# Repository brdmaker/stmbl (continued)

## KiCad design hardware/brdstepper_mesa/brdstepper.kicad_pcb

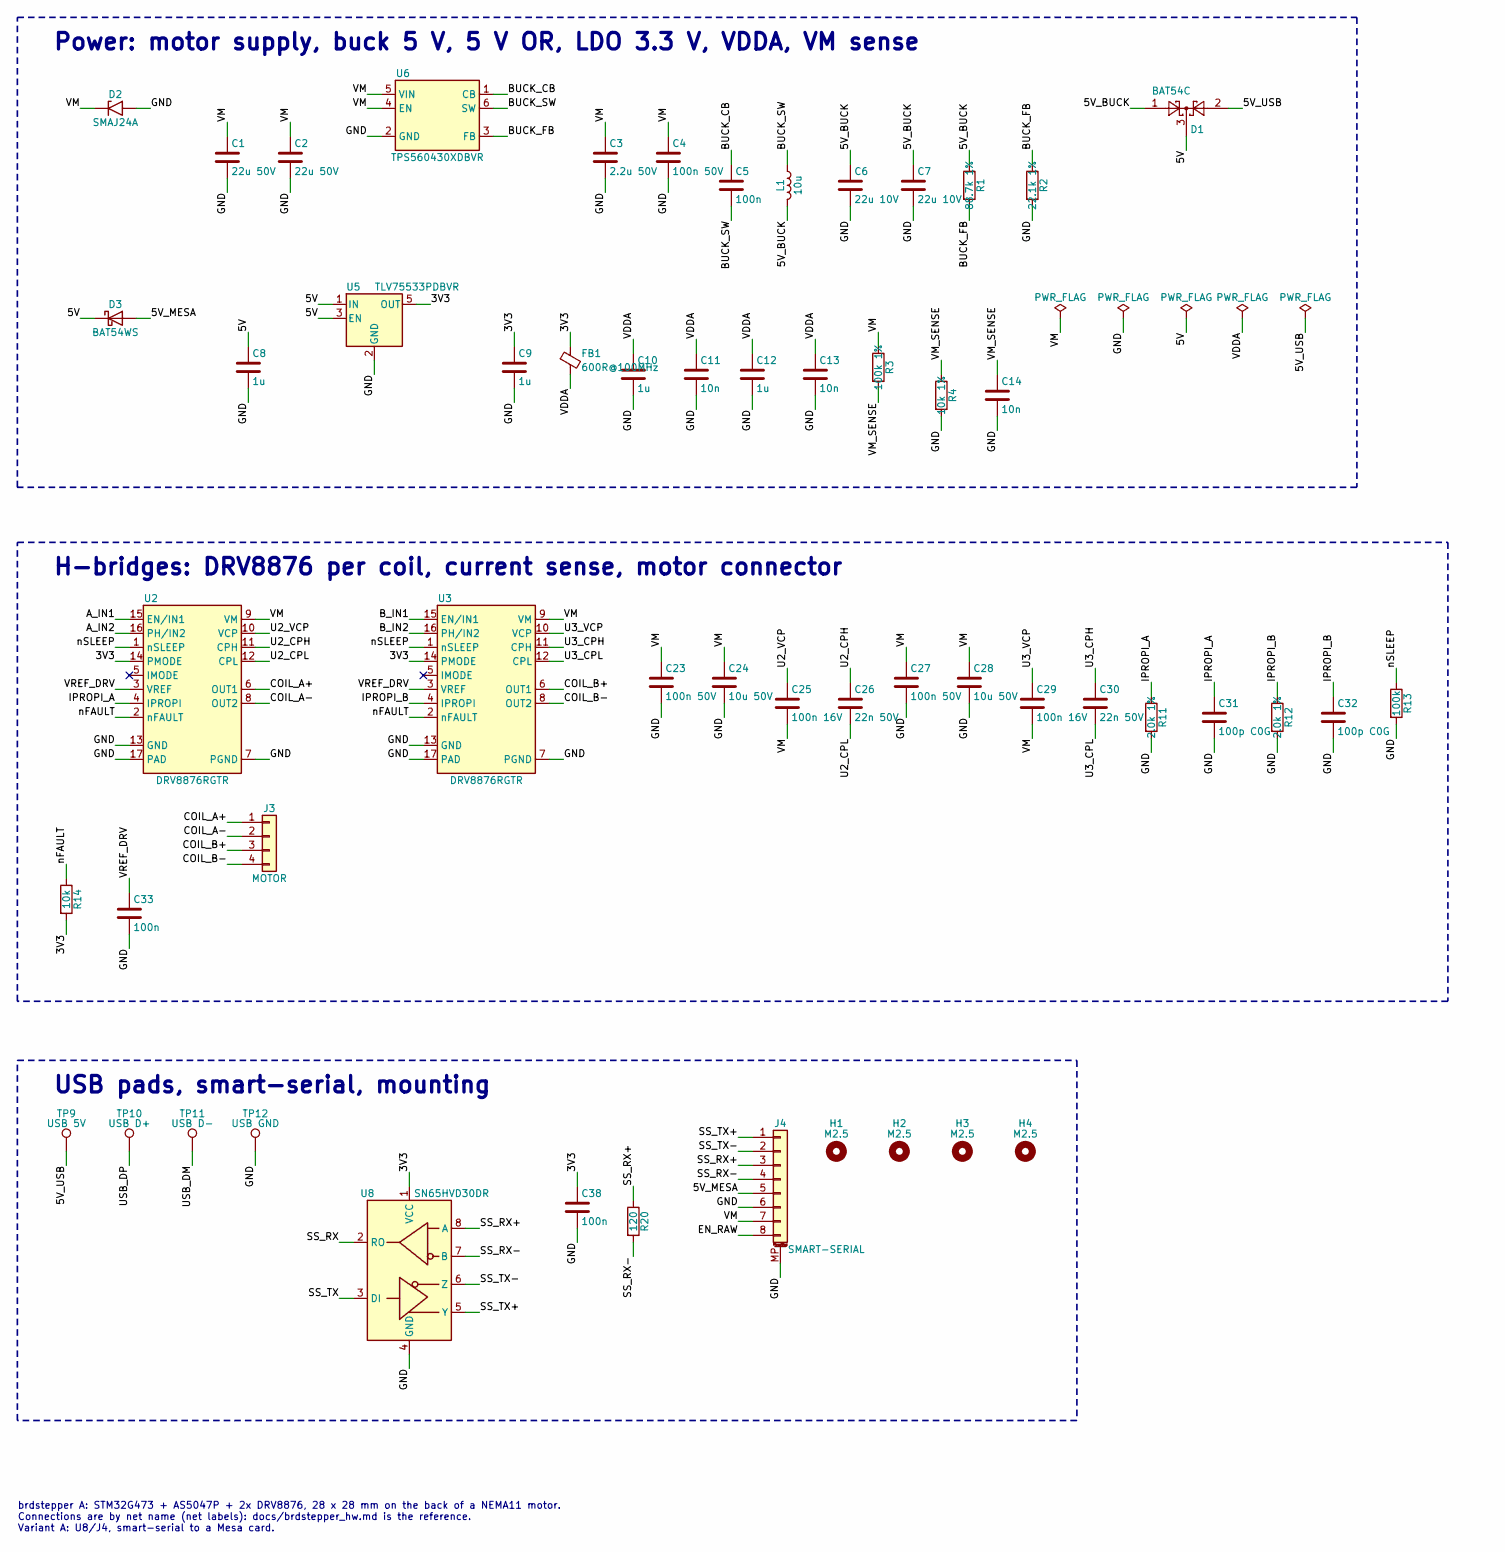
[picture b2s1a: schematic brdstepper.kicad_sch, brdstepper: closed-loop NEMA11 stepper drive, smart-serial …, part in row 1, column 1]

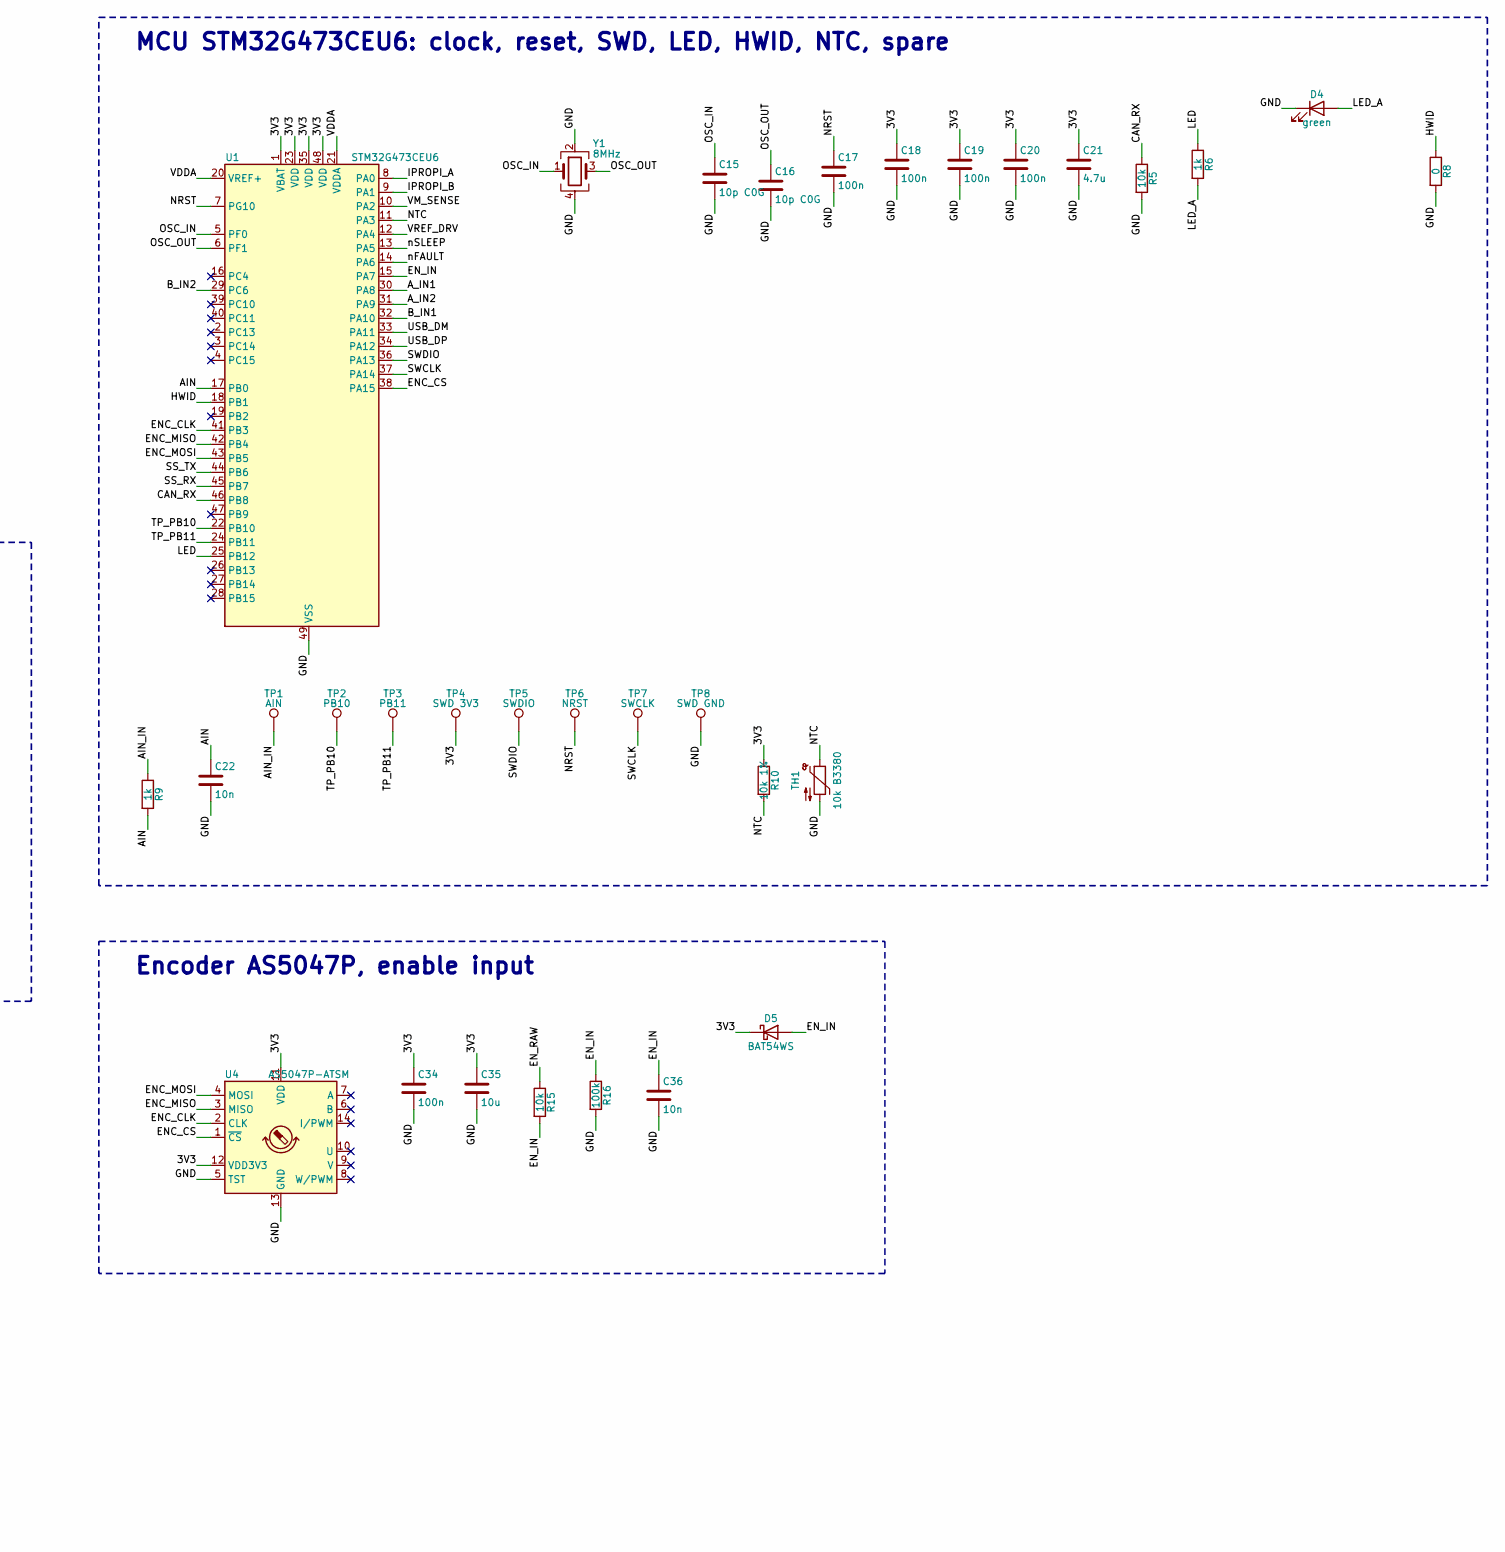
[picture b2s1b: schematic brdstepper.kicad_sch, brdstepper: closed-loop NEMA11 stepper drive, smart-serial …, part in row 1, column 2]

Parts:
C1, C2: 22u 50V; C_1210_3225Metric
C3: 2.2u 50V; C_1206_3216Metric
C4, C23, C27: 100n 50V; C_0603_1608Metric
C5, C17, C18, C19, C20, C33, C34, C38: 100n; C_0603_1608Metric
C6, C7: 22u 10V; C_0805_2012Metric
C8, C9, C10, C12: 1u; C_0603_1608Metric
C11, C13, C14, C22, C36: 10n; C_0603_1608Metric
C15, C16: 10p C0G; C_0603_1608Metric
C21: 4.7u; C_0603_1608Metric
C24, C28: 10u 50V; C_1206_3216Metric
C25, C29: 100n 16V; C_0603_1608Metric
C26, C30: 22n 50V; C_0603_1608Metric
C31, C32: 100p C0G; C_0603_1608Metric
C35: 10u; C_0603_1608Metric
D1: BAT54C; SOT-23
D2: SMAJ24A; D_SMA
D3, D5: BAT54WS; D_SOD-323
D4: green; LED_0603_1608Metric
FB1: 600R@100MHz; L_0603_1608Metric
H1, H2, H3, H4: M2.5; MountingHole_2.7mm_M2.5
J3: MOTOR; PinHeader_1x04_P2.00mm_Vertical
J4: SMART-SERIAL; JST_GH_SM08B-GHS-TB_1x08-1MP_P1.25mm_Horizontal
L1: 10u; L_Taiyo-Yuden_NR-40xx
R1: 88.7k 1%; R_0603_1608Metric
R2: 22.1k 1%; R_0603_1608Metric
R3: 100k 1%; R_0603_1608Metric
R4, R10: 10k 1%; R_0603_1608Metric
R5, R14, R15: 10k; R_0603_1608Metric
R6, R9: 1k; R_0603_1608Metric
R8: 0; R_0603_1608Metric
R11, R12: 2.0k 1%; R_0603_1608Metric
R13, R16: 100k; R_0603_1608Metric
R20: 120; R_0603_1608Metric
TH1: 10k B3380; R_0603_1608Metric
TP1: AIN; TestPoint_Pad_D1.0mm
TP2: PB10; TestPoint_Pad_D1.0mm
TP3: PB11; TestPoint_Pad_D1.0mm
TP4: SWD 3V3; TestPoint_Pad_D1.0mm
TP5: SWDIO; TestPoint_Pad_D1.0mm
TP6: NRST; TestPoint_Pad_D1.0mm
TP7: SWCLK; TestPoint_Pad_D1.0mm
TP8: SWD GND; TestPoint_Pad_D1.0mm
TP9: USB 5V; TestPoint_Pad_D1.0mm
TP10: USB D+; TestPoint_Pad_D1.0mm
TP11: USB D-; TestPoint_Pad_D1.0mm
TP12: USB GND; TestPoint_Pad_D1.0mm
U1: STM32G473CEU6; QFN-48-1EP_7x7mm_P0.5mm_EP5.6x5.6mm
U2, U3: DRV8876RGTR; VQFN-16-1EP_3x3mm_P0.5mm_EP1.68x1.68mm_ThermalVias
U4: AS5047P-ATSM; TSSOP-14_4.4x5mm_P0.65mm
U5: TLV75533PDBVR; SOT-23-5
U6: TPS560430XDBVR; SOT-23-6
U8: SN65HVD30DR; SOIC-8_3.9x4.9mm_P1.27mm
Y1: 8MHz; Crystal_SMD_2016-4Pin_2.0x1.6mm

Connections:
3V3: C9.1, C18.1, C19.1, C20.1, C21.1, C34.1, C35.1, C38.1, D5.1 (K), FB1.1, R10.1, R14.2, TP4.1, U1.1 (VBAT), U1.23 (VDD), U1.35 (VDD), U1.48 (VDD), U2.14 (PMODE), U3.14 (PMODE), U4.11 (VDD), U4.12 (VDD3V3), U5.5 (OUT), U8.1 (VCC)
5V: C8.1, D1.3, D3.1 (K), U5.1 (IN), U5.3 (EN)
5V_BUCK: C6.1, C7.1, D1.1, L1.2, R1.1
5V_MESA: D3.2 (A), J4.5
5V_USB: D1.2, TP9.1
AIN: C22.1, R9.2, U1.17 (PB0)
AIN_IN: R9.1, TP1.1
A_IN1: U1.30 (PA8), U2.15 (EN/IN1)
A_IN2: U1.31 (PA9), U2.16 (PH/IN2)
BUCK_CB: C5.1, U6.1 (CB)
BUCK_FB: R1.2, R2.1, U6.3 (FB)
BUCK_SW: C5.2, L1.1, U6.6 (SW)
B_IN1: U1.32 (PA10), U3.15 (EN/IN1)
B_IN2: U1.29 (PC6), U3.16 (PH/IN2)
CAN_RX: R5.1, U1.46 (PB8)
COIL_A+: J3.1, U2.6 (OUT1)
COIL_A-: J3.2, U2.8 (OUT2)
COIL_B+: J3.3, U3.6 (OUT1)
COIL_B-: J3.4, U3.8 (OUT2)
ENC_CLK: U1.41 (PB3), U4.2 (CLK)
ENC_CS: U1.38 (PA15), U4.1 (~CS)
ENC_MISO: U1.42 (PB4), U4.3 (MISO)
ENC_MOSI: U1.43 (PB5), U4.4 (MOSI)
EN_IN: C36.1, D5.2 (A), R15.2, R16.1, U1.15 (PA7)
EN_RAW: J4.8, R15.1
GND: C1.2, C2.2, C3.2, C4.2, C6.2, C7.2, C8.2, C9.2, C10.2, C11.2, C12.2, C13.2, C14.2, C15.2, C16.2, C17.2, C18.2, C19.2, C20.2, C21.2, C22.2, C23.2, C24.2, C27.2, C28.2, C31.2, C32.2, C33.2, C34.2, C35.2, C36.2, C38.2, D2.2 (A2), D4.1 (K), J4.6, J4.MP (MountPin), R2.2, R4.2, R5.2, R8.2, R11.2, R12.2, R13.2, R16.2, TH1.2, TP8.1, TP12.1, U1.49 (VSS), U2.7 (PGND), U2.13 (GND), U2.17 (PAD), U3.7 (PGND), U3.13 (GND), U3.17 (PAD), U4.5 (TST), U4.13 (GND), U5.2 (GND), U6.2 (GND), U8.4 (GND), Y1.2, Y1.4
HWID: R8.1, U1.18 (PB1)
IPROPI_A: C31.1, R11.1, U1.8 (PA0), U2.4 (IPROPI)
IPROPI_B: C32.1, R12.1, U1.9 (PA1), U3.4 (IPROPI)
LED: R6.1, U1.25 (PB12)
LED_A: D4.2 (A), R6.2
NRST: C17.1, TP6.1, U1.7 (PG10)
NTC: R10.2, TH1.1, U1.11 (PA3)
OSC_IN: C15.1, U1.5 (PF0), Y1.1
OSC_OUT: C16.1, U1.6 (PF1), Y1.3
SS_RX: U1.45 (PB7), U8.2 (RO)
SS_RX+: J4.3, R20.1, U8.8 (A)
SS_RX-: J4.4, R20.2, U8.7 (B)
SS_TX: U1.44 (PB6), U8.3 (DI)
SS_TX+: J4.1, U8.5 (Y)
SS_TX-: J4.2, U8.6 (Z)
SWCLK: TP7.1, U1.37 (PA14)
SWDIO: TP5.1, U1.36 (PA13)
TP_PB10: TP2.1, U1.22 (PB10)
TP_PB11: TP3.1, U1.24 (PB11)
U2_CPH: C26.1, U2.11 (CPH)
U2_CPL: C26.2, U2.12 (CPL)
U2_VCP: C25.1, U2.10 (VCP)
U3_CPH: C30.1, U3.11 (CPH)
U3_CPL: C30.2, U3.12 (CPL)
U3_VCP: C29.1, U3.10 (VCP)
USB_DM: TP11.1, U1.33 (PA11)
USB_DP: TP10.1, U1.34 (PA12)
VDDA: C10.1, C11.1, C12.1, C13.1, FB1.2, U1.20 (VREF+), U1.21 (VDDA)
VM: C1.1, C2.1, C3.1, C4.1, C23.1, C24.1, C25.2, C27.1, C28.1, C29.2, D2.1 (A1), J4.7, R3.1, U2.9 (VM), U3.9 (VM), U6.4 (EN), U6.5 (VIN)
VM_SENSE: C14.1, R3.2, R4.1, U1.10 (PA2)
VREF_DRV: C33.1, U1.12 (PA4), U2.3 (VREF), U3.3 (VREF)
nFAULT: R14.1, U1.14 (PA6), U2.2 (nFAULT), U3.2 (nFAULT)
nSLEEP: R13.1, U1.13 (PA5), U2.1 (nSLEEP), U3.1 (nSLEEP)

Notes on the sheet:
Power: motor supply, buck 5 V, 5 V OR, LDO 3.3 V, VDDA, VM sense
MCU STM32G473CEU6: clock, reset, SWD, LED, HWID, NTC, spare
H-bridges: DRV8876 per coil, current sense, motor connector
Encoder AS5047P, enable input
USB pads, smart-serial, mounting
brdstepper A: STM32G473 + AS5047P + 2x DRV8876, 28 x 28 mm on the back of a NEMA11 motor. Connections are by net name (net labels): docs/brdstepper_hw.md is the reference. Variant A: U8/J4, smart-serial to a Mesa card.

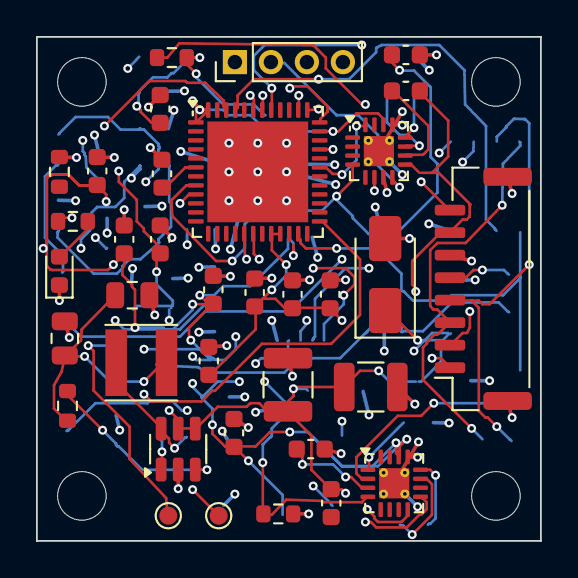
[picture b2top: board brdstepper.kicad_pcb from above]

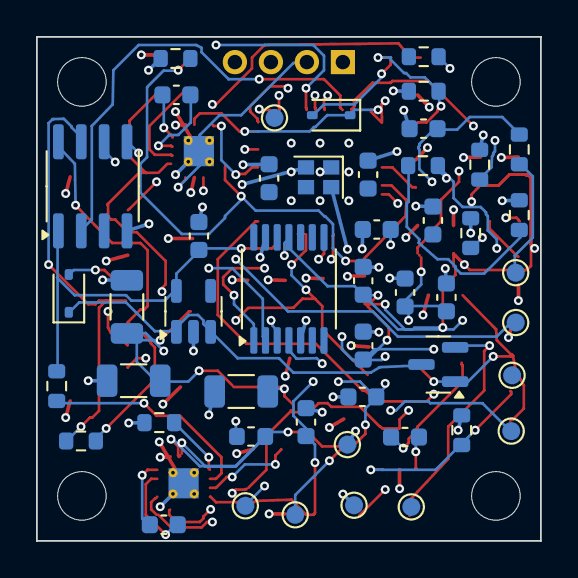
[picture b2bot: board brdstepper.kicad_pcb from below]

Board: 4 copper layers, 28.0 x 28.0 mm, 87 parts (48 on the bottom side), 59 nets.

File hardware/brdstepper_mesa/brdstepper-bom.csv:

References,Qty,Value,Footprint,Variant,Notes
C1 C2,2,22u 50V,C_1210_3225Metric,,"bulk, near the drivers; bulk"
C3,1,2.2u 50V,C_1206_3216Metric,,buck input
C4 C23 C27,3,100n 50V,C_0603_1608Metric,,"buck input, at the pin; U2 VM, at the pin; U3 VM, at the pin"
C5 C17 C18 C19 C20 C33 C34 C38,8,100n,C_0603_1608Metric,,bootstrap; VDD (23); VDD (35); VDD (48); ✱ per the 3.3 V application circuit; U8
C6 C7,2,22u 10V,C_0805_2012Metric,,buck output
C8 C9 C10 C12,4,1u,C_0603_1608Metric,,LDO input; LDO output; VDDA (21); VREF+ (20)
C11 C13 C14 C22 C36,5,10n,C_0603_1608Metric,,VDDA (21); VREF+ (20)
C15 C16,2,10p C0G,C_0603_1608Metric,,✱ per the crystal's CL
C21,1,4.7u,C_0603_1608Metric,,
C24 C28,2,10u 50V,C_1206_3216Metric,,U2 VM; U3 VM
C25 C29,2,100n 16V,C_0603_1608Metric,,U2 VCP; U3 VCP
C26 C30,2,22n 50V,C_0603_1608Metric,,U2 flying; U3 flying
C31 C32,2,100p C0G,C_0603_1608Metric,,≤ 100 pF (or not fitted)
C35,1,10u,C_0603_1608Metric,,
D1,1,BAT54C,SOT-23,,"5 V OR: buck, USB"
D2,1,SMAJ24A,D_SMA,,TVS ✱ (for 24 V; lower for less)
D3 D5,2,BAT54WS,D_SOD-323,,5 V OR: the Mesa port (variant A); clamp to 3V3 ✱
D4,1,green,LED_0603_1608Metric,,
FB1,1,600R@100MHz,L_0603_1608Metric,,VDDA / VREF+
J3,1,MOTOR,PinHeader_1x04_P2.00mm_Vertical,,"A+ A- B+ B-: solder pads for the motor leads, on the board edge (§4.7 allows pads; a JST-PH 4 doesn't fit the 28 mm board)"
J4,1,SMART-SERIAL,JST_GH_SM08B-GHS-TB_1x08-1MP_P1.25mm_Horizontal,,"variant A; to the Mesa card's RJ45 ✱. Also the motor supply (VM 12-36 V, EN: enable / estop, 3.3-24 V): no separate supply connector. ✱ GH is 1 A per contact"
L1,1,10u,L_Taiyo-Yuden_NR-40xx,,"✱ NR4018, ≥ 0.6 A"
R1,1,88.7k 1%,R_0603_1608Metric,,5.02 V with 22.1k (VREF 1.00 V)
R2,1,22.1k 1%,R_0603_1608Metric,,
R3,1,100k 1%,R_0603_1608Metric,,§4.8: 3.0 V at 33 V
R4 R10,2,10k 1%,R_0603_1608Metric,,NTC pull-up
R5 R14 R15,3,10k,R_0603_1608Metric,,PB8-BOOT0 low until the option bytes are set; EN_IN 3.3-24 V ✱
R6 R9,2,1k,R_0603_1608Metric,,spare analog input
R8,1,0,R_0603_1608Metric,,"§6 HWID: variant A, 0 Ω: HWID 0 V"
R11 R12,2,2.0k 1%,R_0603_1608Metric,,§5: 3.3 V = 1.65 A
R13 R16,2,100k,R_0603_1608Metric,,
R20,1,120,R_0603_1608Metric,,RX termination (variant A)
TH1,1,10k B3380,R_0603_1608Metric,,close to the drivers
U1,1,STM32G473CEU6,QFN-48-1EP_7x7mm_P0.5mm_EP5.6x5.6mm,,"exposed pad: the only VSS / VSSA; solder it, with vias to the In1 GND plane (add them in layout). Spare: PB2, PB14, PB15, PC4, PC10, PC11, PC13"
U2 U3,2,DRV8876RGTR,VQFN-16-1EP_3x3mm_P0.5mm_EP1.68x1.68mm_ThermalVias,,"IMODE (5) open: fixed off-time, overcurrent latched; PMODE high: IN1/IN2 PWM"
U4,1,AS5047P-ATSM,TSSOP-14_4.4x5mm_P0.65mm,,"on the bottom, centred on the shaft ✱; 3.3 V mode: VDD and VDD3V3 together"
U5,1,TLV75533PDBVR,SOT-23-5,,"3.3 V, ≥ 150 mA ✱"
U6,1,TPS560430XDBVR,SOT-23-6,,buck to 5 V ✱ (values per its datasheet)
U8,1,SN65HVD30DR,SOIC-8_3.9x4.9mm_P1.27mm,,"variant A ✱ (the MAX3490's pinout, as the SN65HVD30's)"
Y1,1,8MHz,Crystal_SMD_2016-4Pin_2.0x1.6mm,,✱ CL

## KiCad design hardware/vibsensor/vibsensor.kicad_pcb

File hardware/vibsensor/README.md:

# vibsensor KiCad project

The vibration and temperature sensor of [docs/vibsensor.md](../../docs/vibsensor.md),
for the firmware in [vibsensor/](../../vibsensor/README.md): a KiCad 7
project with the schematic, a placed (not routed) 32 × 18 mm board shaped to
the enclosure, and a BOM. The enclosure concept is in [enclosure/](enclosure/README.md).

**State:**
- **Schematic:** complete, one sheet, checked against the part list
  (`make sch`: 50 parts, 33 nets).
- **Board:**
  - 32 × 18 mm, chamfered to the enclosure "Shard", four layers, a GND plane
    on In1.Cu (not filled: press B in the editor).
  - Every footprint placed with its nets; DRC clean but for the unrouted
    connections.
  - **Not routed:** the placement is a starting point for the layout.
- **To check against datasheets** (✱ in each part's *Note* and the BOM):
  - the IIS3DWB's pinout and decoupling (DS12569);
  - the TMP117's pinout and exposed pad;
  - the TCAN1044V, drawn with the TJA1042T-3 symbol (same pinout);
  - the buck converter's inductor;
  - the crystal's load capacitors;
  - the M8 sockets' pin order (no CiA standard for M8 4-pin).

## The circuit

| section | parts |
|---|---|
| supply | J1 (IN) and J3 (OUT), the two M8 sockets' leads, wired 1:1 (1 V+, 2 CAN_H, 3 GND, 4 CAN_L), so supply and bus pass through to the next sensor; D1 reverse polarity; D2 TVS; U2 TPS560430 buck to 5 V (the transceiver); U3 TLV75533 to 3.3 V; ferrite-filtered VDDA and the accelerometer's own 3V3_ACC; R3 / R4, the bus voltage to PA0 |
| MCU | U1 STM32G473CEU6, pins as `vibsensor/inc/vs.h`; 8 MHz crystal; LED; J2 Tag-Connect TC2030 pads for SWD (programmed before potting) |
| sensors | U4 IIS3DWB on SPI1 (PA4-7, INT1 / INT2 on PB0 / PB1); U5 TMP117 on I2C2 (PA8 / PA9, ALERT on PA10), address 0x48 |
| CAN | U6 TCAN1044V (VCC 5 V, VIO 3.3 V, STB on PB13); no termination on the board: the last sensor's OUT takes an M8 terminator plug (120 Ω inside) |

**On the board:**
- **Top:** the MCU at the centre, the supply, SWD; the M8 leads' pads in
  two rows along the long edges by the tail's corners, J1 (IN, −y) and J3
  (OUT, +y), where the sockets are.
- **Bottom** (facing the enclosure's floor, over the M6 hole):
  - the IIS3DWB at the centre;
  - the TMP117 beside it;
  - the transceiver.
- **Mounting:** two M2 holes at ±9 mm on the long axis hold the board to
  the floor's bosses before potting.
- **Nose:** the narrow end (+x) is the sensor's X axis.

## Generated: edit `gen/parts.py` and `gen/board.py`

`make` runs `hardware/kigen` (see `hardware/brdstepper/README.md`):
- `sch` and `check`: the schematic, and its netlist against the part list;
- `pcb`: placement (redone: hand edits to the board are lost);
- `drc`, `bom`, `doc`: DRC, the BOM, the PDF and the render.

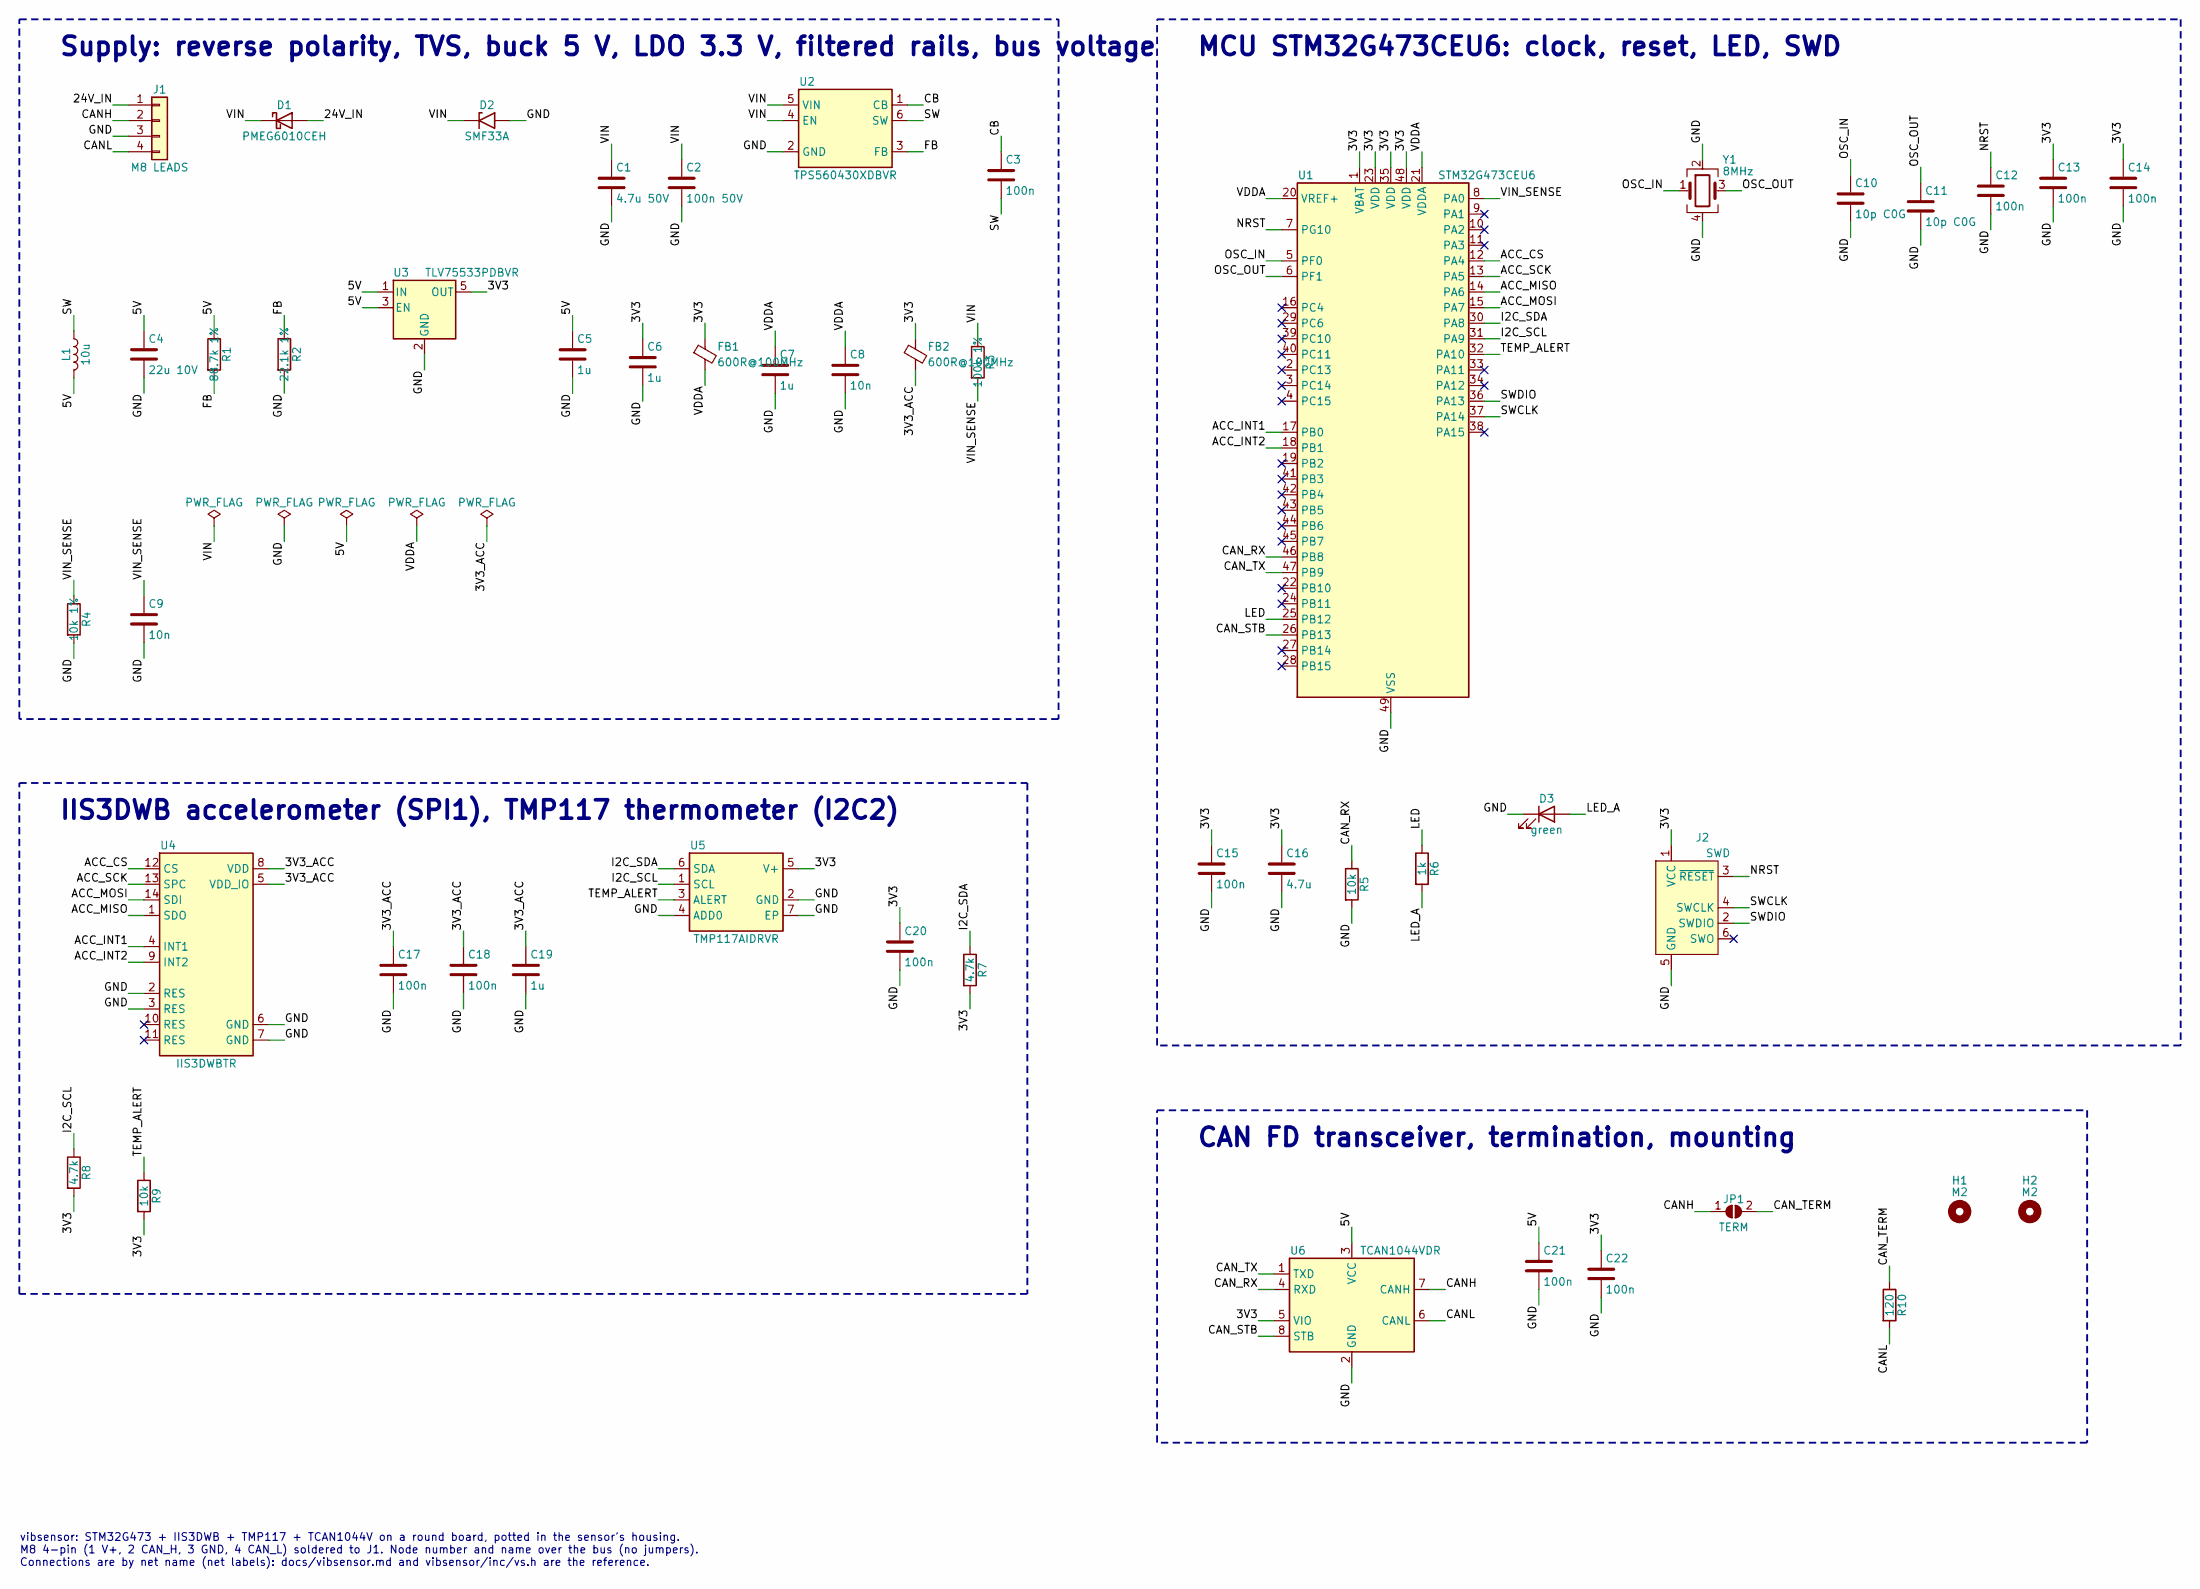
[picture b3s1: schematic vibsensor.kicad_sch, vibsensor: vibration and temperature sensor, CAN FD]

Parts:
C1: 4.7u 50V; C_1206_3216Metric
C2: 100n 50V; C_0402_1005Metric
C3, C12, C13, C14, C15, C17, C18, C20, C21, C22: 100n; C_0402_1005Metric
C4: 22u 10V; C_0805_2012Metric
C5, C6, C7, C19: 1u; C_0402_1005Metric
C8, C9: 10n; C_0402_1005Metric
C10, C11: 10p C0G; C_0402_1005Metric
C16: 4.7u; C_0603_1608Metric
D1: PMEG6010CEH; D_SOD-123F
D2: SMF33A; D_SMF
D3: green; LED_0603_1608Metric
FB1, FB2: 600R@100MHz; L_0402_1005Metric
H1, H2: M2; MountingHole_2.2mm_M2
J1: M8 LEADS; PinHeader_1x04_P2.00mm_Vertical
J2: SWD; Tag-Connect_TC2030-IDC-NL_2x03_P1.27mm_Vertical
JP1: TERM; SolderJumper-2_P1.3mm_Open_RoundedPad1.0x1.5mm
L1: 10u; L_Taiyo-Yuden_NR-30xx
R1: 88.7k 1%; R_0402_1005Metric
R2: 22.1k 1%; R_0402_1005Metric
R3: 100k 1%; R_0402_1005Metric
R4: 10k 1%; R_0402_1005Metric
R5, R9: 10k; R_0402_1005Metric
R6: 1k; R_0402_1005Metric
R7, R8: 4.7k; R_0402_1005Metric
R10: 120; R_0402_1005Metric
U1: STM32G473CEU6; QFN-48-1EP_7x7mm_P0.5mm_EP5.6x5.6mm
U2: TPS560430XDBVR; SOT-23-6
U3: TLV75533PDBVR; SOT-23-5
U4: IIS3DWBTR; LGA-14_3x2.5mm_P0.5mm_LayoutBorder3x4y
U5: TMP117AIDRVR; WSON-6-1EP_2x2mm_P0.65mm_EP1x1.6mm
U6: TCAN1044VDR; SOIC-8_3.9x4.9mm_P1.27mm
Y1: 8MHz; Crystal_SMD_2016-4Pin_2.0x1.6mm

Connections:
3V3: C6.1, C13.1, C14.1, C15.1, C16.1, C20.1, C22.1, FB1.1, FB2.1, J2.1 (VCC), R7.2, R8.2, R9.2, U1.1 (VBAT), U1.23 (VDD), U1.35 (VDD), U1.48 (VDD), U3.5 (OUT), U5.5 (V+), U6.5 (VIO)
3V3_ACC: C17.1, C18.1, C19.1, FB2.2, U4.5 (VDD_IO), U4.8 (VDD)
5V: C4.1, C5.1, C21.1, L1.2, R1.1, U3.1 (IN), U3.3 (EN), U6.3 (VCC)
24V_IN: D1.2 (A), J1.1; also elsewhere on the board
ACC_CS: U1.12 (PA4), U4.12 (CS)
ACC_INT1: U1.17 (PB0), U4.4 (INT1)
ACC_INT2: U1.18 (PB1), U4.9 (INT2)
ACC_MISO: U1.14 (PA6), U4.1 (SDO)
ACC_MOSI: U1.15 (PA7), U4.14 (SDI)
ACC_SCK: U1.13 (PA5), U4.13 (SPC)
CANH: J1.2, JP1.1 (A), U6.7 (CANH); also elsewhere on the board
CANL: J1.4, R10.2, U6.6 (CANL); also elsewhere on the board
CAN_RX: R5.1, U1.46 (PB8), U6.4 (RXD)
CAN_STB: U1.26 (PB13), U6.8 (STB)
CAN_TX: U1.47 (PB9), U6.1 (TXD)
CB: C3.1, U2.1 (CB)
FB: R1.2, R2.1, U2.3 (FB)
GND: C1.2, C2.2, C4.2, C5.2, C6.2, C7.2, C8.2, C9.2, C10.2, C11.2, C12.2, C13.2, C14.2, C15.2, C16.2, C17.2, C18.2, C19.2, C20.2, C21.2, C22.2, D2.2 (A2), D3.1 (K), J1.3, J2.5 (GND), R2.2, R4.2, R5.2, U1.49 (VSS), U2.2 (GND), U3.2 (GND), U4.2 (RES), U4.3 (RES), U4.6 (GND), U4.7 (GND), U5.2 (GND), U5.4 (ADD0), U5.7 (EP), U6.2 (GND), Y1.2, Y1.4; also elsewhere on the board
I2C_SCL: R8.1, U1.31 (PA9), U5.1 (SCL)
I2C_SDA: R7.1, U1.30 (PA8), U5.6 (SDA)
LED: R6.1, U1.25 (PB12)
LED_A: D3.2 (A), R6.2
NRST: C12.1, J2.3 (~RESET), U1.7 (PG10)
unnamed: JP1.2 (B), R10.1
OSC_IN: C10.1, U1.5 (PF0), Y1.1
OSC_OUT: C11.1, U1.6 (PF1), Y1.3
SW: C3.2, L1.1, U2.6 (SW)
SWCLK: J2.4 (SWCLK), U1.37 (PA14)
SWDIO: J2.2 (SWDIO), U1.36 (PA13)
TEMP_ALERT: R9.1, U1.32 (PA10), U5.3 (ALERT)
VDDA: C7.1, C8.1, FB1.2, U1.20 (VREF+), U1.21 (VDDA)
VIN: C1.1, C2.1, D1.1 (K), D2.1 (A1), R3.1, U2.4 (EN), U2.5 (VIN)
VIN_SENSE: C9.1, R3.2, R4.1, U1.8 (PA0)

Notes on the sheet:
Supply: reverse polarity, TVS, buck 5 V, LDO 3.3 V, filtered rails, bus voltage
MCU STM32G473CEU6: clock, reset, LED, SWD
IIS3DWB accelerometer (SPI1), TMP117 thermometer (I2C2)
CAN FD transceiver, termination, mounting
vibsensor: STM32G473 + IIS3DWB + TMP117 + TCAN1044V on a round board, potted in the sensor's housing. M8 4-pin (1 V+, 2 CAN_H, 3 GND, 4 CAN_L) soldered to J1. Node number and name over the bus (no jumpers). Connections are by net name (net labels): docs/vibsensor.md and vibsensor/inc/vs.h are the r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

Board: 4 copper layers, 49 parts (19 on the bottom side), 32 nets, no tracks yet.

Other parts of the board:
J3: M8 OUT; PinHeader_1x04_P2.00mm_Vertical

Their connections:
24V_IN: J3.1; also elsewhere on the board
CANH: J3.2; also elsewhere on the board
CANL: J3.4; also elsewhere on the board
GND: J3.3; also elsewhere on the board

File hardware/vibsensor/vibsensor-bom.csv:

References,Qty,Value,Footprint,Variant,Notes
C1,1,4.7u 50V,C_1206_3216Metric,,input
C2,1,100n 50V,C_0402_1005Metric,,at the buck's VIN
C3 C12 C13 C14 C15 C17 C18 C20 C21 C22,10,100n,C_0402_1005Metric,,bootstrap; VDD (23); VDD (35); VDD (48); VDD (8) ✱; VDD_IO (5); TMP117; VCC; VIO
C4,1,22u 10V,C_0805_2012Metric,,buck output
C5 C6 C7 C19,4,1u,C_0402_1005Metric,,LDO input; LDO output
C8 C9,2,10n,C_0402_1005Metric,,
C10 C11,2,10p C0G,C_0402_1005Metric,,✱ per the crystal's CL
C16,1,4.7u,C_0603_1608Metric,,
D1,1,PMEG6010CEH,D_SOD-123F,,reverse polarity
D2,1,SMF33A,D_SMF,,TVS ✱ (pad 1 the cathode)
D3,1,green,LED_0603_1608Metric,,seen through the potting? ✱
FB1 FB2,2,600R@100MHz,L_0402_1005Metric,,MCU analog; the accelerometer's own supply
J1,1,M8 LEADS,PinHeader_1x04_P2.00mm_Vertical,,"the M8 socket's leads, M8 order: 1 V+, 2 CAN_H, 3 GND, 4 CAN_L ✱"
L1,1,10u,L_Taiyo-Yuden_NR-30xx,,"✱ NR3015, >= 0.3 A"
R1,1,88.7k 1%,R_0402_1005Metric,,5.02 V with 22.1k (VREF 1.00 V)
R2,1,22.1k 1%,R_0402_1005Metric,,
R3,1,100k 1%,R_0402_1005Metric,,bus voltage: 2.7 V at 30 V
R4,1,10k 1%,R_0402_1005Metric,,
R5 R9,2,10k,R_0402_1005Metric,,PB8-BOOT0 low until the option bytes are set; ALERT is open drain
R6,1,1k,R_0402_1005Metric,,
R7 R8,2,4.7k,R_0402_1005Metric,,
R10,1,120,R_0402_1005Metric,,
U1,1,STM32G473CEU6,QFN-48-1EP_7x7mm_P0.5mm_EP5.6x5.6mm,,"exposed pad: the only VSS / VSSA; vias to the GND plane. PA0 VIN_SENSE, PA4-7 SPI1, PB0/PB1 INT1/2, PA8/9 I2C2, PA10 ALERT, PB8/9 FDCAN1, PB12 LED, PB13 STB"
U2,1,TPS560430XDBVR,SOT-23-6,,"buck to 5 V, as brdstepper's ✱"
U3,1,TLV75533PDBVR,SOT-23-5,,3.3 V
U4,1,IIS3DWBTR,LGA-14_3x2.5mm_P0.5mm_LayoutBorder3x4y,,"SPI mode 3; RES 2, 3 to GND, 10, 11 open (DS12569) ✱; near the mounting stud"
U5,1,TMP117AIDRVR,WSON-6-1EP_2x2mm_P0.65mm_EP1x1.6mm,,"address 0x48 (ADD0 to GND); on the mounting face, thermally bonded ✱"
U6,1,TCAN1044VDR,SOIC-8_3.9x4.9mm_P1.27mm,,"CAN FD to 5 Mbit/s; the TJA1042T-3's pinout, as the TCAN1044V's ✱"
Y1,1,8MHz,Crystal_SMD_2016-4Pin_2.0x1.6mm,,✱ CL

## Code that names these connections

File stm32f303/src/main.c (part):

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  MX_ADC3_Init();
  MX_ADC4_Init();
  MX_DAC_Init();
  //COMP1 in+ pa1(ADC1_IN2)  in- pa4(dac1_ch1)
  COMP1->CSR = COMP_CSR_COMPxINSEL_2 | COMP1_CSR_COMP1OUTSEL_2 | COMP_CSR_COMPxEN;
  //COMP2 in+ pa7(ADC2_IN4)  in- pa4(dac1_ch1) COMP_CSR_COMPxNONINSEL
  COMP2->CSR = COMP_CSR_COMPxINSEL_2 | COMP2_CSR_COMP2OUTSEL_0 | COMP2_CSR_COMP2OUTSEL_1 | COMP_CSR_COMPxEN;
  //COMP4 in+ pb0(ADC3_IN12) in- pa4(dac1_ch1)
  COMP4->CSR = COMP_CSR_COMPxINSEL_2 | COMP4_CSR_COMP4OUTSEL_0 | COMP4_CSR_COMP4OUTSEL_1 | COMP_CSR_COMPxEN;
  MX_OPAMP1_Init();
  MX_OPAMP2_Init();
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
